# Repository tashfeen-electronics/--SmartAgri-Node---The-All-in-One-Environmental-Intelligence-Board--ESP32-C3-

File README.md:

# 🌾 SmartAgri Node — The All-in-One Environmental Intelligence Board— ESP32-C3 Environmental Monitoring PCB

A custom 4-layer PCB designed in KiCad for smart agriculture and environmental data logging — built around the **ESP32-C3-WROOM-02-H4**, with onboard sensing, local storage, and off-grid power management.

---

## 🚀 Overview

## 🌾 SmartAgri Node — The All-in-One Environmental Intelligence Board

*A masterclass in compact IoT engineering — built for the field, engineered for the future.*

Powered by the **ESP32-C3-WROOM-02-H4**, this board isn't just a sensor node — it's a complete edge-computing ecosystem packed into a single, elegant design. Whether you're building smart farms, weather networks, or next-gen IoT products, this board is your foundation.

### 🚀 Flagship Applications

- **🌱 Precision Agriculture Systems** — Real-time climate intelligence (temp, humidity, pressure, light) empowers farmers to optimize irrigation, planting, and harvest cycles like never before
- **☀️ Off-Grid Solar Monitoring Stations** — Autonomous, self-charging design (USB-C + battery + MCP73871 power management) means true "install and forget" reliability in remote locations
- **📡 Enterprise-Grade IoT Weather Networks** — Wi-Fi/BLE connectivity turns every unit into a live data point in a scalable, cloud-connected sensor mesh
- **💾 Mission-Critical Data Logging** — Onboard microSD ensures zero data loss, even in connectivity dead zones — perfect for research-grade field studies
- **🔊 Smart Environmental Surveillance** — Integrated mic input opens doors to acoustic monitoring: pest detection, livestock sounds, equipment health diagnostics
- **🔆 Intelligent Light Management** — TEMT6000 sensor enables automated greenhouse shading, grow-light control, and crop exposure analytics
- **🔌 Plug-and-Play Expansion Platform** — I2C/GPIO breakout headers make this a launchpad for custom sensor arrays: soil moisture, pH, EC, CO2, and beyond
- **🛡️ Industrial-Grade Power Protection** — ESD protection, fuse safeguarding, and regulated 3.3V rail deliver rock-solid reliability in harsh outdoor conditions
- **☁️ OTA-Ready Firmware Architecture** — Onboard SPI flash means remote fleets can be updated instantly — no truck rolls, no manual reflashing
- **🎓 Premier Prototyping & Education Platform** — USB-C programming, dedicated BOOT/RESET buttons, and SPI test points make this the go-to dev board for makers, students, and R&D teams alike

### 💎 Why This Board Stands Out

One design. Ten industries. Infinite possibilities — from **precision farming** to **smart cities**, **environmental research** to **industrial IoT**. This isn't just a PCB — it's a **scalable platform** ready to power the next generation of connected, autonomous sensing solutions.

---

## 🌾 Applications

- **Smart agriculture field monitoring** — logs temperature, humidity, pressure, and light intensity across crop fields or greenhouses
- **Solar/battery-powered remote sensor node** — runs unattended in the field, rechargeable via USB-C or solar panel
- **Soil/climate data logging station** — SD card backup for areas with weak or no Wi-Fi coverage
- **IoT weather station** — pushes live BME280 readings to a cloud dashboard or local server
- **Sunlight exposure tracking** — monitors sun exposure for crop growth optimization
- **Acoustic/pest monitoring** — mic input can detect insect activity, animal presence, or equipment sound
- **Expandable sensor hub** — I2C/GPIO headers for adding soil moisture, pH, or EC sensors
- **Battery-backed edge logger** — continues sensing during power outages or disconnection
- **OTA-capable firmware node** — onboard SPI flash supports remote firmware updates
- **General-purpose outdoor IoT dev board** — reusable prototyping platform beyond agriculture

---

## 🧩 Hardware Overview

### 🧠 Core Processing & Connectivity
| Component | Part | Purpose |
|---|---|---|
| U3 | ESP32-C3-WROOM-02-H4 | Main MCU — Wi-Fi/BLE, RISC-V core, chosen for wireless field data transmission without an external radio module |
| U4 | CP2102N | USB-to-UART bridge for programming/serial debug over USB-C |
| U2 | W25Q32JVSSIQ (32Mbit SPI Flash) | Extra non-volatile storage for OTA updates and log buffering |
| J3 | GSD090012SEU (microSD slot) | Local offline data logging when Wi-Fi is unavailable |

### 🌡️ Sensors
| Component | Part | Purpose |
|---|---|---|
| U6 | BME280 | Temperature, humidity & barometric pressure sensing |
| Q1 | TEMT6000X01 | Ambient light intensity sensing for crop exposure analysis |
| U7 | MAX4466EXK | Mic amplifier for acoustic sensing (pest/environmental sound) |

### 🔋 Power Management
| Component | Part | Purpose |
|---|---|---|
| J1 | USB-C (2338792-1) | Primary power/data input |
| J2 | JST connector (B2B-PH-SM4-TB) | Li-ion/LiPo battery input |
| U1 | MCP73871 | Battery charge management + power path — charges while running on USB |
| VR1 | LM1117MPX-3.3 | Regulates supply to a clean 3.3V rail |
| U5 | USBLC6-2SC6 | ESD protection on USB data lines |
| F1 | 0ZCH0110AF2E | Resettable fuse — overcurrent protection |
| Q2, Q3 | BC817 | Power switching/load gating for sleep-mode power savings |
| MK1 | CMC-5042PF-AC | Inductor/choke for power line filtering |

### 🕹️ User Interface
| Component | Part | Purpose |
|---|---|---|
| S1 | BOOT button | Puts ESP32 into flashing/bootloader mode |
| S2 | RESET button | Manual MCU reset |
| D1, D5 | Blue LEDs | Status indicators |
| D2, D6 | Green LEDs | Status indicators |
| D3, D4 | Red LEDs | Fault/error indicators |

### 🔧 Debug & Expansion
| Component | Purpose |
|---|---|
| TP1–TP5 | SPI bus test points (MOSI, MISO, SCLK, CS, CS-SD) for debugging flash/SD card |
| J4 | 4-pin header — I2C expansion (GND/SCL/SDA/3.3V) for external sensors |
| J5 | 5-pin header — additional GPIO/power expansion |

### ⚙️ Passives
- **Capacitors (C1–C25):** Decoupling and bulk capacitance for clean power delivery, especially during Wi-Fi transmit bursts
- **Resistors (R1–R35):** Pull-ups (I2C/reset lines), LED current limiting, and voltage divider/feedback networks

---

## 🧱 PCB Stackup — Why 4 Layers?

This board uses a **4-layer stackup (Signal / GND / PWR / Signal)** instead of a simpler 2-layer design, chosen specifically for better signal integrity given the mix of RF, digital, analog, and power circuitry on one small board.

**Benefits realized:**
- ✅ Dedicated, uninterrupted ground plane — critical for ESP32-C3 RF performance and reducing noise coupling into analog sensors
- ✅ Shorter, controlled return paths for high-speed SPI signals (flash + SD card), reducing EMI and reflections
- ✅ Dedicated power plane for cleaner, lower-impedance power delivery — especially during Wi-Fi TX current spikes
- ✅ Better isolation between noisy switching regulator circuitry and sensitive analog front-end (mic amp, light sensor)
- ✅ Tighter, more professional routing without sacrificing signal quality

---

## 🛠️ Tools Used

- **KiCad** — schematic capture, PCB layout, and 3D visualization

---

## 📸 Board Preview

*(Add board render/photo here)*

---

## 📋 Bill of Materials

Full BOM with quantities and footprints is available in <a href="https://github.com/tashfeen-electronics/--SmartAgri-Node---The-All-in-One-Environmental-Intelligence-Board--ESP32-C3-/blob/main/ESP32%20Project/bom/ibom.html" class="button">BOM</a>

---

## 📄 License

<a href="https://github.com/tashfeen-electronics/--SmartAgri-Node---The-All-in-One-Environmental-Intelligence-Board--ESP32-C3-/blob/main/LICENSE" class="button">
  ***LICENSE***
</a>

---

## 🙌 Author

**Tashfeen Electronics**
Designed with ❤️ in KiCad

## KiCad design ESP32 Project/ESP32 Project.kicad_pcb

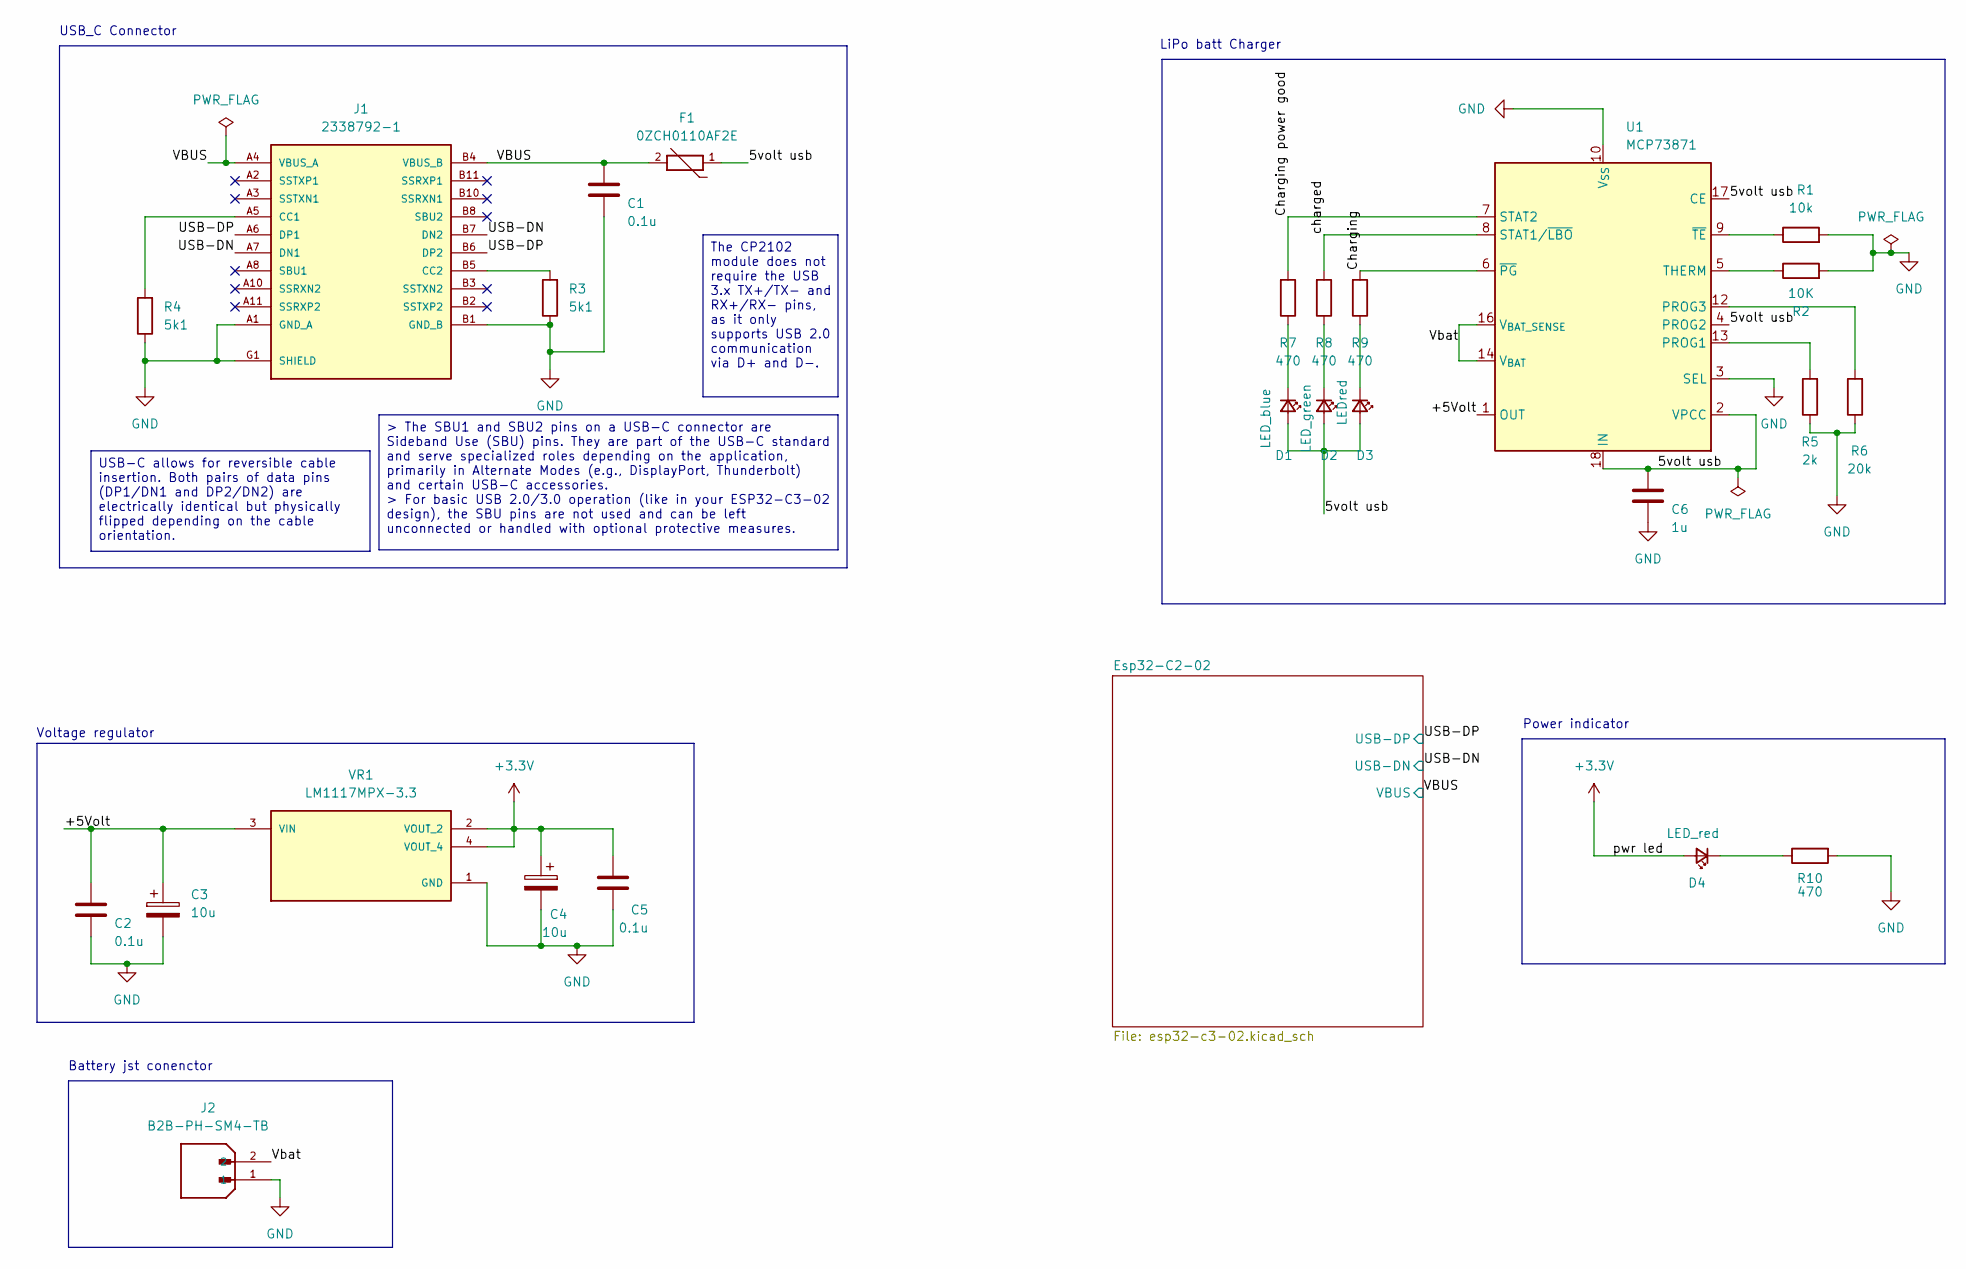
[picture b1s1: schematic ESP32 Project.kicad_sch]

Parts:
C1, C2, C5: 0.1u; C_0805_2012Metric
C3, C4: 10u; CP_EIA-3216-12_Kemet-S
C6: 1u; C_0805_2012Metric
D1: LED_blue; LED_0805_2012Metric_Pad1.15x1.40mm_HandSolder
D2: LED_green; LED_0805_2012Metric_Pad1.15x1.40mm_HandSolder
D3: LEDred; LED_0805_2012Metric_Pad1.15x1.40mm_HandSolder
D4: LED_red; LED_0805_2012Metric_Pad1.15x1.40mm_HandSolder
F1: 0ZCH0110AF2E; FUSC3225X100N; PARTREV Apr2023
J1: 2338792-1; TE_2338792-1; PARTREV A1
J2: B2B-PH-SM4-TB; JST_B2B-PH-SM4-TB; PARTREV N/A
R1: 10k; R_0805_2012Metric
R2: 10K; R_0805_2012Metric
R3, R4: 5k1; R_0805_2012Metric
R5: 2k; R_0805_2012Metric
R6: 20k; R_0805_2012Metric
R7, R8, R9, R10: 470; R_0805_2012Metric
U1: MCP73871; QFN-20-1EP_4x4mm_P0.5mm_EP2.5x2.5mm
VR1: LM1117MPX-3.3; VREG_LM1117MPX-3.3; PARTREV O

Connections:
+3.3V: C4.1, C5.1, D4.2 (A), VR1.2 (VOUT_2), VR1.4 (VOUT_4); also elsewhere on the board
/5volt usb: C6.1, D1.2 (A), D2.2 (A), D3.2 (A), F1.1, U1.2 (VPCC), U1.4 (PROG2), U1.17 (CE), U1.18 (IN), U1.19 (IN)
/+5Volt: C2.1, C3.1, U1.1 (OUT), U1.20 (OUT), VR1.3 (VIN)
/Charging: R9.2, U1.6 (~PG)
/Charging power good: R7.2, U1.7 (STAT2)
/USB-DN: J1.A7 (DN1), J1.B7 (DN2); also elsewhere on the board
/USB-DP: J1.A6 (DP1), J1.B6 (DP2); also elsewhere on the board
/Vbat: J2.2, U1.14 (V_{BAT}), U1.15 (V_{BAT}), U1.16 (V_{BAT_SENSE})
/charged: R8.2, U1.8 (STAT1/~LBO)
GND: C1.2, C2.2, C3.2, C4.2, C5.2, C6.2, J1.A1 (GND_A), J1.A12 (GND_A), J1.B1 (GND_B), J1.B12 (GND_B), J1.G1 (SHIELD), J1.G2 (SHIELD), J1.G3 (SHIELD), J1.G4 (SHIELD), J1.G5 (SHIELD), J1.G6 (SHIELD), J2.1, R1.2, R2.2, R3.1, R4.1, R5.1, R6.1, R10.2, U1.3 (SEL), U1.10 (V_{SS}), U1.11 (V_{SS}), U1.21 (V_{SS}), VR1.1 (GND); also elsewhere on the board
unnamed: D1.1 (K), R7.1
unnamed: D2.1 (K), R8.1
unnamed: D3.1 (K), R9.1
unnamed: D4.1 (K), R10.1
unnamed: J1.A5 (CC1), R4.2
unnamed: J1.B5 (CC2), R3.2
unnamed: R5.2, U1.13 (PROG1)
unnamed: R6.2, U1.12 (PROG3)
unnamed: R2.1, U1.5 (THERM)
unnamed: R1.1, U1.9 (~TE)
VBUS_A: C1.1, F1.2, J1.A4 (VBUS_A), J1.A9 (VBUS_A), J1.B4 (VBUS_B), J1.B9 (VBUS_B); also elsewhere on the board

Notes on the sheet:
Power indicator
USB_C Connector
Voltage regulator
LiPo batt Charger
Battery jst conenctor
USB-C allows for reversible cable insertion. Both pairs of data pins (DP1/DN1 and DP2/DN2) are electrically identical but physically flipped depending on the cable orientation.
The CP2102 module does not require the USB 3.x TX+/TX- and RX+/RX- pins, as it only supports USB 2.0 communication via D+ and D-.
> The SBU1 and SBU2 pins on a USB-C connector are Sideband Use (SBU) pins. They are part of the USB-C standard and serve specialized roles depending on the application, primarily in Alternate Modes (e.g., DisplayPort, Thunderbolt) and certain USB-C accessories. > For basic USB 2.0/3.0 operation (li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

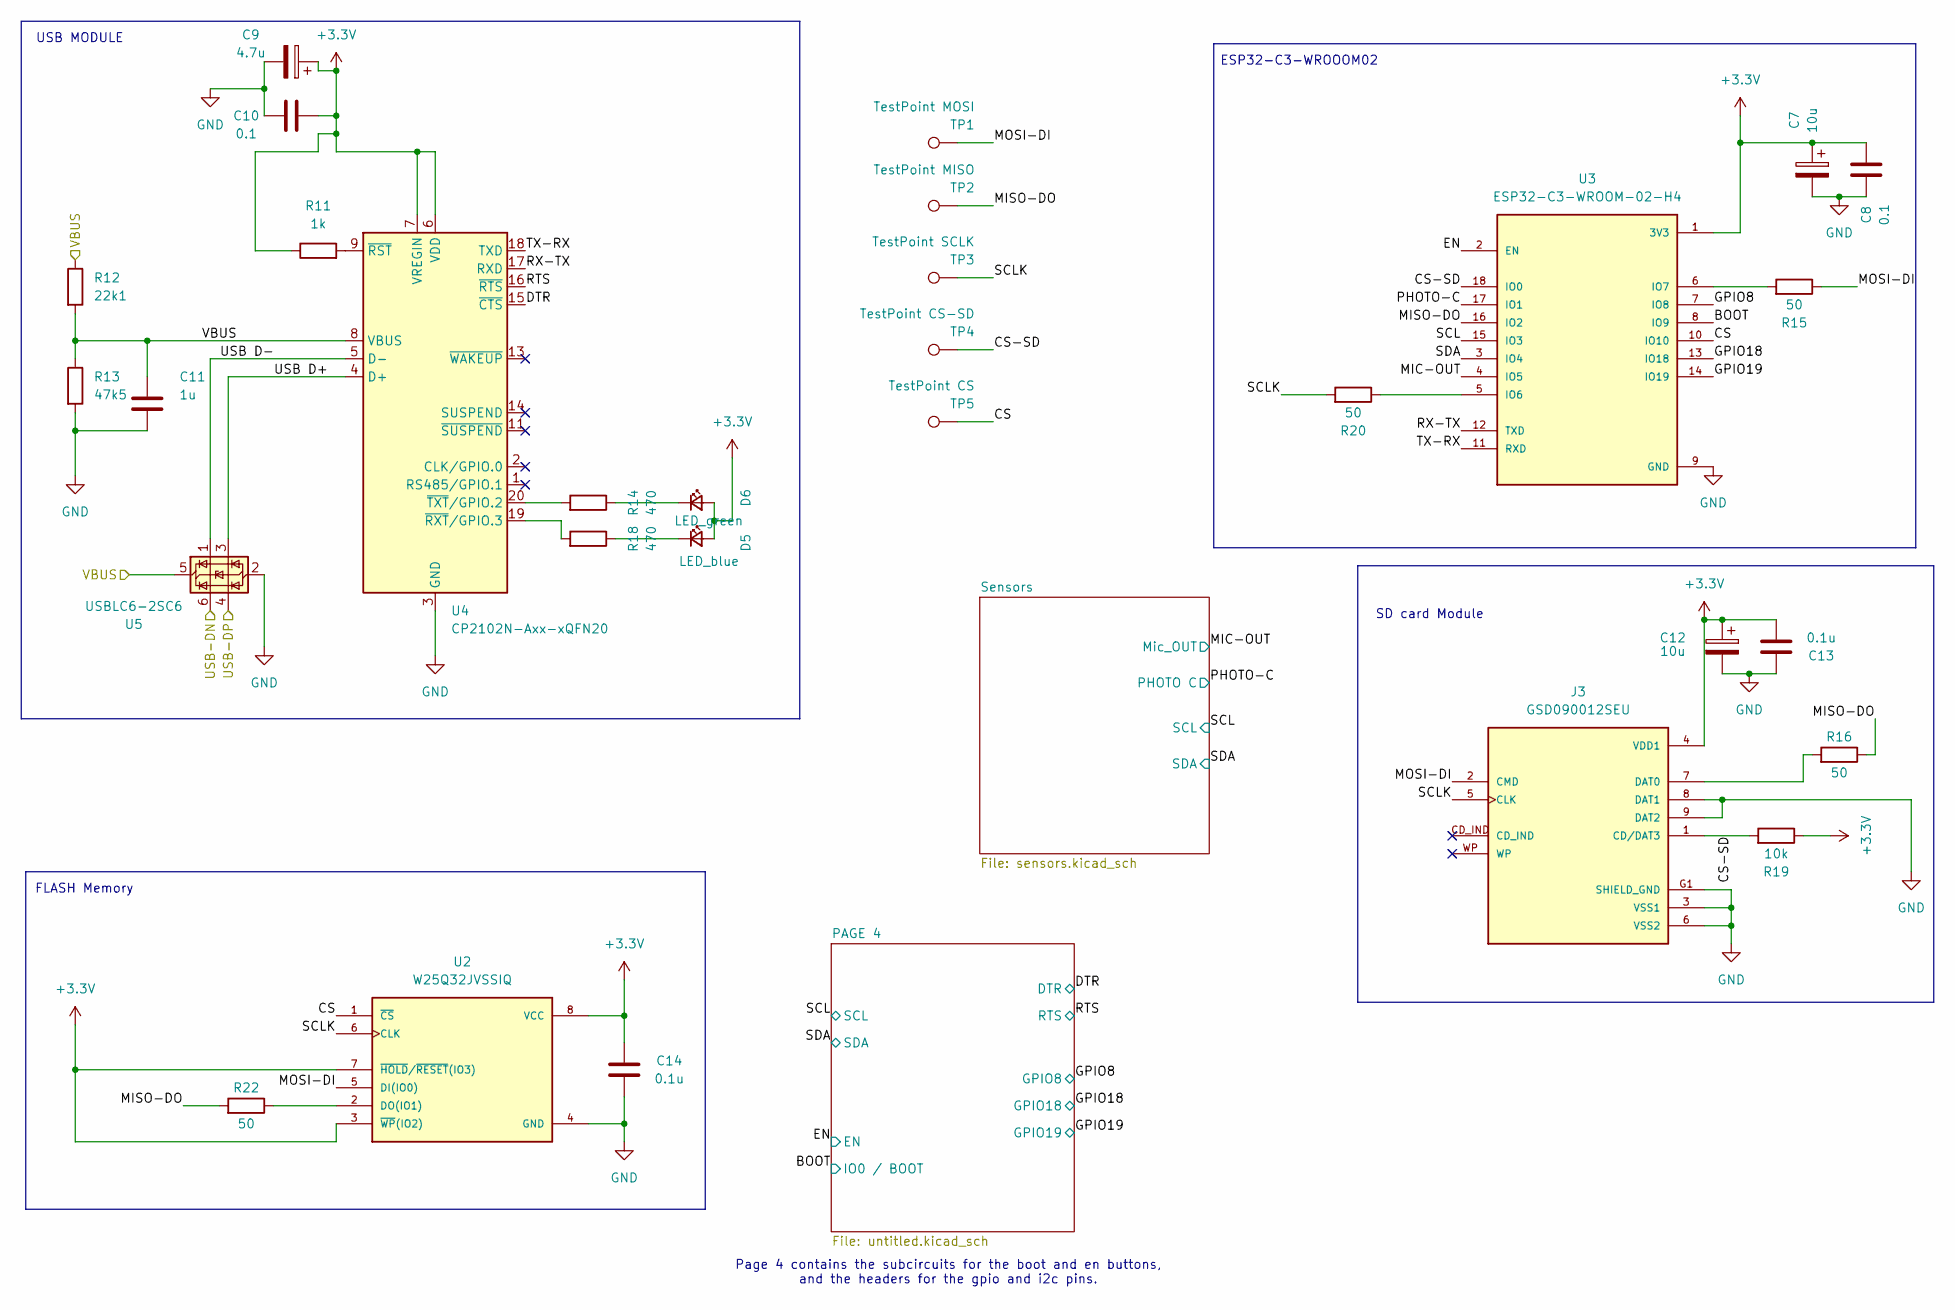
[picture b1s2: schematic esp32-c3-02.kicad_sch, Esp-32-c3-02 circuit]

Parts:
C7, C12: 10u; CP_EIA-3216-12_Kemet-S
C8, C10: 0.1; C_0805_2012Metric
C9: 4.7u; CP_EIA-3216-12_Kemet-S
C11: 1u; C_0805_2012Metric
C13, C14: 0.1u; C_0805_2012Metric
D5: LED_blue; LED_0805_2012Metric_Pad1.15x1.40mm_HandSolder
D6: LED_green; LED_0805_2012Metric_Pad1.15x1.40mm_HandSolder
J3: GSD090012SEU; AMPHENOL_GSD090012SEU; PARTREV E
R11: 1k; R_0805_2012Metric
R12: 22k1; R_0805_2012Metric
R13: 47k5; R_0805_2012Metric
R14, R18: 470; R_0805_2012Metric
R15, R16, R20, R22: 50; R_0805_2012Metric
R19: 10k; R_0805_2012Metric
TP1: TestPoint MOSI; TestPoint_Pad_D1.0mm
TP2: TestPoint MISO; TestPoint_Pad_D1.0mm
TP3: TestPoint SCLK; TestPoint_Pad_D1.0mm
TP4: TestPoint CS-SD; TestPoint_Pad_D1.0mm
TP5: TestPoint CS; TestPoint_Pad_D1.0mm
U2: W25Q32JVSSIQ; SOIC127P790X216-8N; M_PART_NUMBER W25QXX
U3: ESP32-C3-WROOM-02-H4; MODULE_ESP32-C3-WROOM-02-H4
U4: CP2102N-Axx-xQFN20; QFN-20-1EP_3x3mm_P0.45mm_EP1.6x1.6mm
U5: USBLC6-2SC6; SOT-23-6

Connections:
+3.3V: C7.1, C8.1, C9.1, C10.1, C12.1, C13.1, C14.2, D5.2 (A), D6.2 (A), J3.4 (VDD1), R11.1, R19.1, U2.3 (~WP(IO2)), U2.7 (~HOLD/~RESET(IO3)), U2.8 (VCC), U3.1 (3V3), U4.6 (VDD), U4.7 (VREGIN); also elsewhere on the board
/Esp32-C2-02/BOOT: U3.8 (IO9); also elsewhere on the board
/Esp32-C2-02/CS: TP5.1 (1_1), U2.1 (~CS), U3.10 (IO10)
/Esp32-C2-02/CS-SD: J3.1 (CD/DAT3), R19.2, TP4.1 (1_1), U3.18 (IO0)
/Esp32-C2-02/DTR: U4.15 (~CTS); also elsewhere on the board
/Esp32-C2-02/EN: U3.2 (EN); also elsewhere on the board
/Esp32-C2-02/GPIO8: U3.7 (IO8); also elsewhere on the board
/Esp32-C2-02/GPIO18: U3.13 (IO18); also elsewhere on the board
/Esp32-C2-02/GPIO19: U3.14 (IO19); also elsewhere on the board
/Esp32-C2-02/MIC-OUT: U3.4 (IO5); also elsewhere on the board
/Esp32-C2-02/MISO-DO: R16.1, R22.2, TP2.1 (1_1), U3.16 (IO2)
/Esp32-C2-02/MOSI-DI: J3.2 (CMD), R15.1, TP1.1 (1_1), U2.5 (DI(IO0))
/Esp32-C2-02/PHOTO-C: U3.17 (IO1); also elsewhere on the board
/Esp32-C2-02/RTS: U4.16 (~RTS); also elsewhere on the board
/Esp32-C2-02/RX-TX: U3.12 (TXD), U4.17 (RXD)
/Esp32-C2-02/SCL: U3.15 (IO3); also elsewhere on the board
/Esp32-C2-02/SCLK: J3.5 (CLK), R20.2, TP3.1 (1_1), U2.6 (CLK)
/Esp32-C2-02/SDA: U3.3 (IO4); also elsewhere on the board
/Esp32-C2-02/TX-RX: U3.11 (RXD), U4.18 (TXD)
/Esp32-C2-02/USB D+: U4.4 (D+), U5.3 (I/O2)
/Esp32-C2-02/USB D-: U4.5 (D-), U5.1 (I/O1)
/USB-DN: U5.6 (I/O1); also elsewhere on the board
/USB-DP: U5.4 (I/O2); also elsewhere on the board
GND: C7.2, C8.2, C9.2, C10.2, C11.2, C12.2, C13.2, C14.1, J3.3 (VSS1), J3.6 (VSS2), J3.8 (DAT1), J3.9 (DAT2), J3.G1 (SHIELD_GND), J3.G2 (SHIELD_GND), J3.G3 (SHIELD_GND), J3.G4 (SHIELD_GND), R13.2, U2.4 (GND), U3.9 (GND), U3.19 (GND), U3.20 (GND), U3.21 (GND), U3.22 (GND), U3.23 (GND), U3.24 (GND), U3.25 (GND), U3.26 (GND), U3.27 (GND), U3.28 (GND), U3.29 (GND), U3.30 (GND), U3.31 (GND), U3.32 (GND), U3.33 (GND), U3.34 (GND), U3.35 (GND), U3.36 (GND), U3.37 (GND), U3.38 (GND), U3.39 (GND), U4.3 (GND), U4.12 (GND), U4.21 (GND), U5.2 (GND); also elsewhere on the board
unnamed: D5.1 (K), R18.1
unnamed: D6.1 (K), R14.1
unnamed: J3.7 (DAT0), R16.2
unnamed: R22.1, U2.2 (DO(IO1))
unnamed: R20.1, U3.5 (IO6)
unnamed: R15.2, U3.6 (IO7)
unnamed: R11.2, U4.9 (~RST)
unnamed: R18.2, U4.19 (~RXT/GPIO.3)
unnamed: R14.2, U4.20 (~TXT/GPIO.2)
VBUS_A: C11.1, R12.1, R12.2, R13.1, U4.8 (VBUS), U5.5 (VBUS); also elsewhere on the board

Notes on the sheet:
USB MODULE
SD card Module
Page 4 contains the subcircuits for the boot and en buttons, and the headers for the gpio and i2c pins.
ESP32-C3-WROOOM02
FLASH Memory

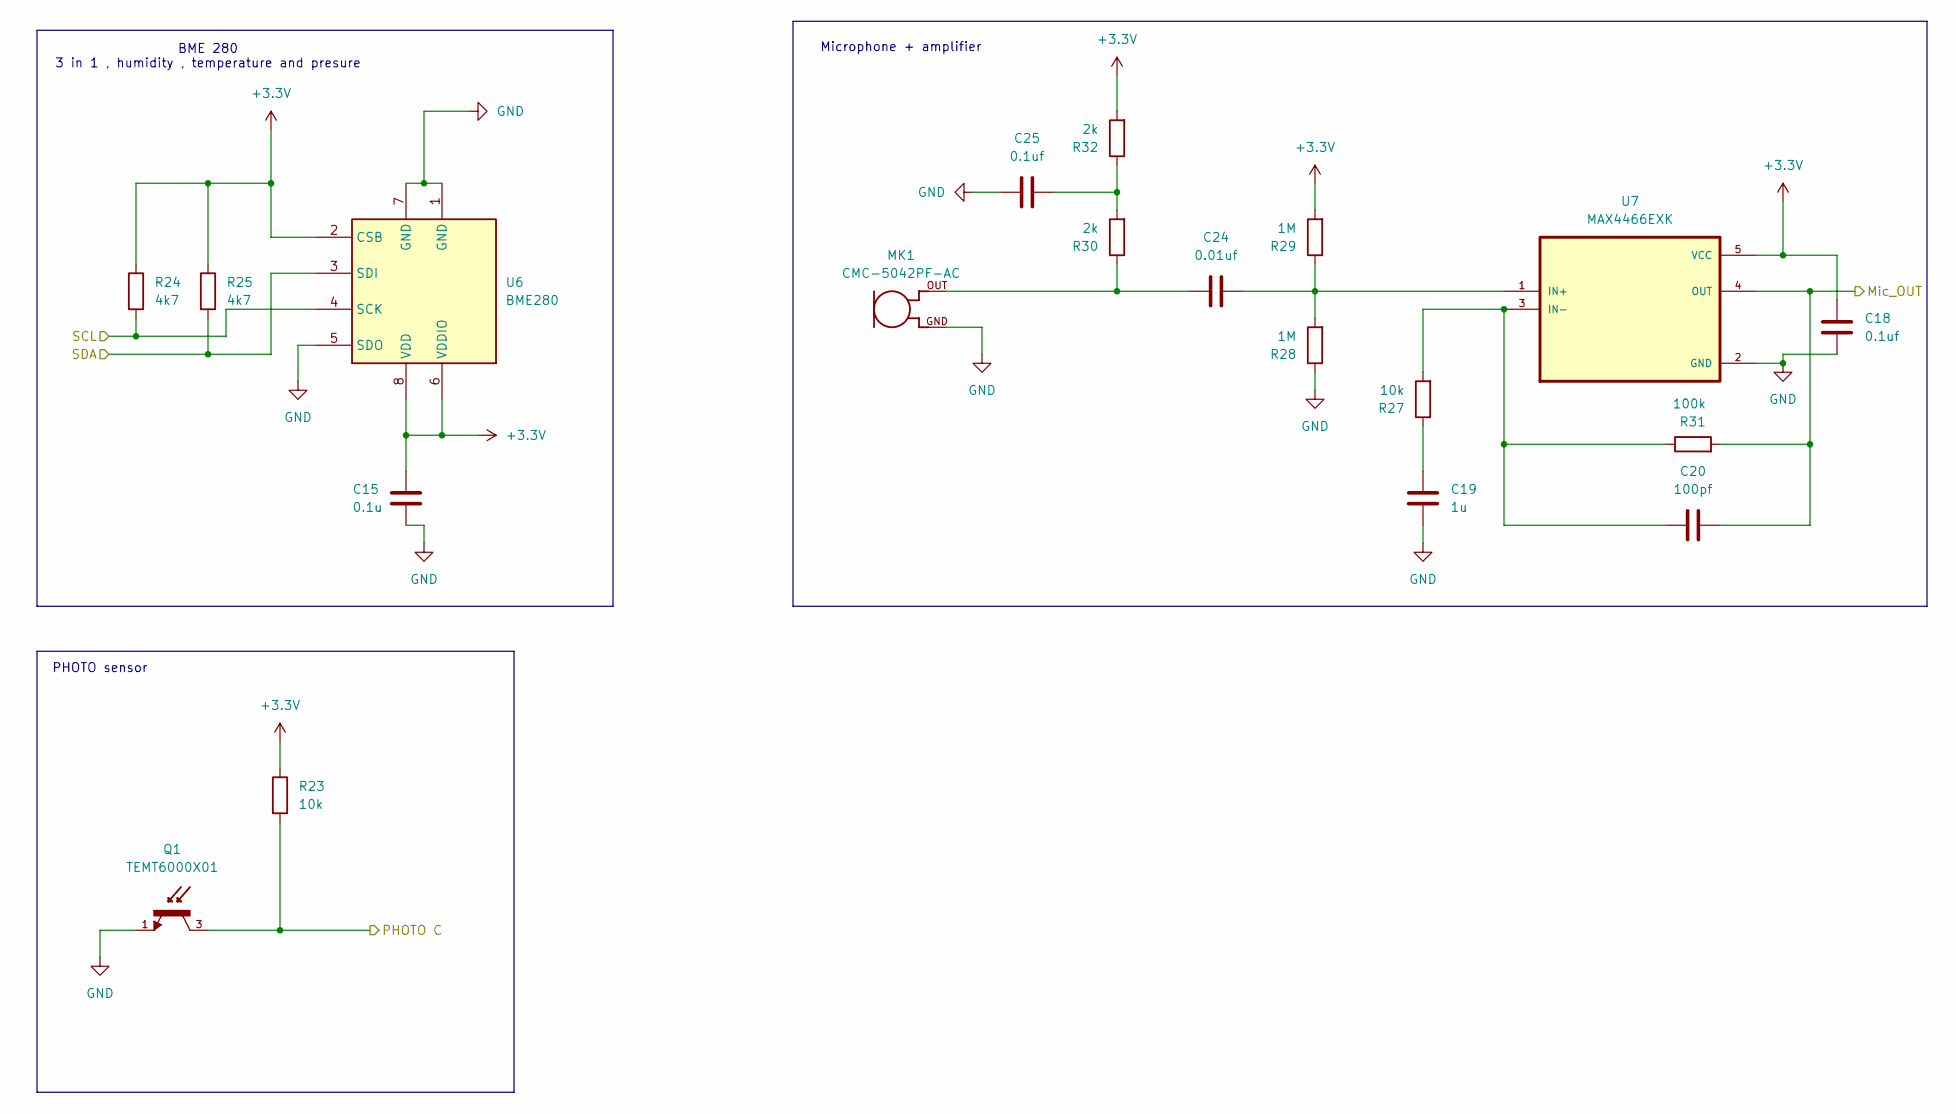
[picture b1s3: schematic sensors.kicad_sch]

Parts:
C15: 0.1u; C_0805_2012Metric
C18, C25: 0.1uf; C_0805_2012Metric
C19: 1u; C_0805_2012Metric
C20: 100pf; C_0805_2012Metric
C24: 0.01uf; C_0805_2012Metric
MK1: CMC-5042PF-AC; CUI_CMC-5042PF-AC
Q1: TEMT6000X01; TRANS_TEMT6000X01; PARTREV 1.9
R23, R27: 10k; R_0805_2012Metric
R24, R25: 4k7; R_0805_2012Metric
R28, R29: 1M; R_0805_2012Metric
R30, R32: 2k; R_0805_2012Metric
R31: 100k; R_0805_2012Metric
U6: BME280; Bosch_LGA-8_2.5x2.5mm_P0.65mm_ClockwisePinNumbering
U7: MAX4466EXK; SOT65P210X110-5N; DigiKey_Part_Number MAX4466EXK+CT-ND

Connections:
+3.3V: C15.2, C18.2, R23.1, R24.1, R25.1, R29.2, R32.2, U6.2 (CSB), U6.6 (VDDIO), U6.8 (VDD), U7.5 (VCC); also elsewhere on the board
/Esp32-C2-02/MIC-OUT: C20.1, R31.2, U7.4 (OUT); also elsewhere on the board
/Esp32-C2-02/PHOTO-C: Q1.3, R23.2; also elsewhere on the board
/Esp32-C2-02/SCL: R24.2, U6.4 (SCK); also elsewhere on the board
/Esp32-C2-02/SDA: R25.2, U6.3 (SDI); also elsewhere on the board
GND: C15.1, C18.1, C19.2, C25.2, MK1.GND, Q1.1, R28.1, U6.1 (GND), U6.5 (SDO), U6.7 (GND), U7.2 (GND); also elsewhere on the board
unnamed: C19.1, R27.1
unnamed: C24.2, MK1.OUT, R30.1
unnamed: C25.1, R30.2, R32.1
unnamed: C24.1, R28.2, R29.1, U7.1 (IN+)
unnamed: C20.2, R27.2, R31.1, U7.3 (IN-)

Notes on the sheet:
BME 280 3 in 1 , humidity , temperature and presure
PHOTO sensor
Microphone + amplifier

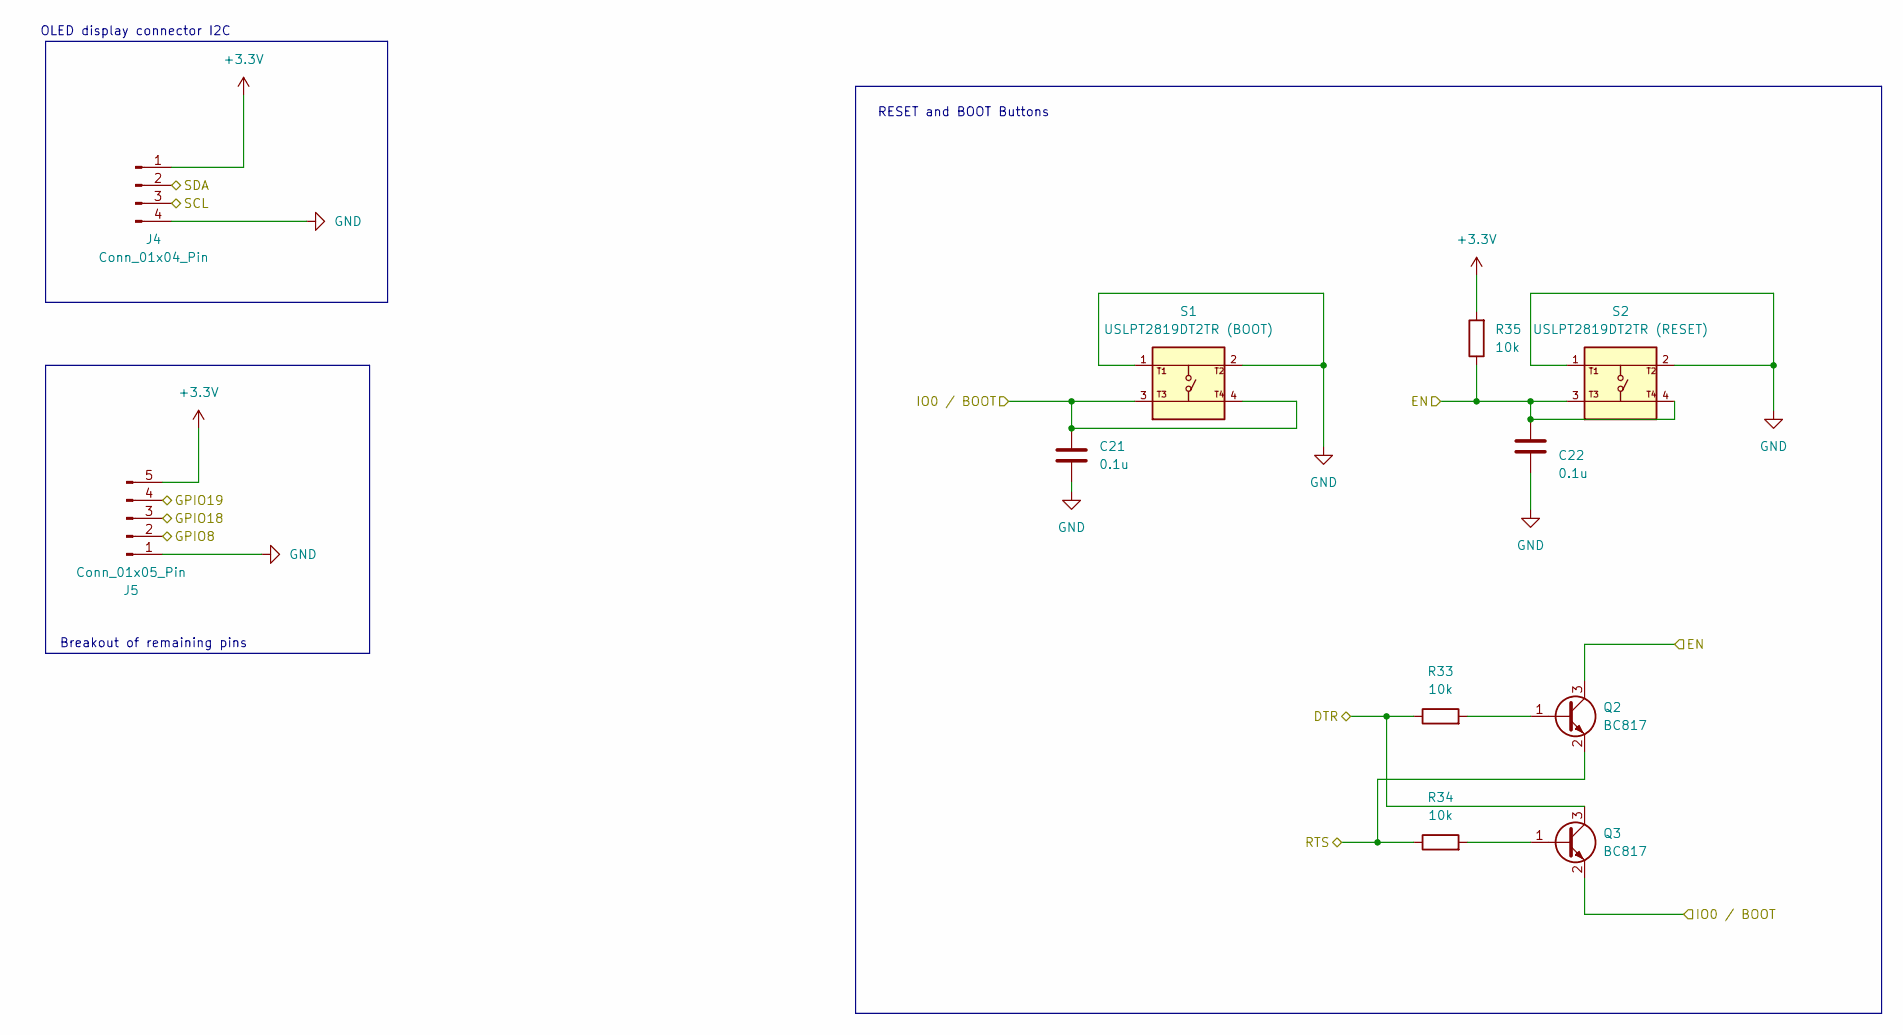
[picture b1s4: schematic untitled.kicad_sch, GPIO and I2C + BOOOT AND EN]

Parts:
C21, C22: 0.1u; C_0805_2012Metric
J4: Conn_01x04_Pin; PinHeader_1x04_P2.54mm_Vertical
J5: Conn_01x05_Pin; PinHeader_1x05_P2.54mm_Vertical
Q2, Q3: BC817; SOT-23
R33, R34, R35: 10k; R_0805_2012Metric
S1: USLPT2819DT2TR (BOOT); SW_USLPT2819DT2TR; PARTREV P
S2: USLPT2819DT2TR (RESET); SW_USLPT2819DT2TR; PARTREV P

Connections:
+3.3V: J4.1, J5.5, R35.2; also elsewhere on the board
/Esp32-C2-02/BOOT: C21.1, Q3.2 (E), S1.3, S1.4; also elsewhere on the board
/Esp32-C2-02/DTR: Q3.3 (C), R33.1; also elsewhere on the board
/Esp32-C2-02/EN: C22.1, Q2.3 (C), R35.1, S2.3, S2.4; also elsewhere on the board
/Esp32-C2-02/GPIO8: J5.2; also elsewhere on the board
/Esp32-C2-02/GPIO18: J5.3; also elsewhere on the board
/Esp32-C2-02/GPIO19: J5.4; also elsewhere on the board
/Esp32-C2-02/RTS: Q2.2 (E), R34.1; also elsewhere on the board
/Esp32-C2-02/SCL: J4.3; also elsewhere on the board
/Esp32-C2-02/SDA: J4.2; also elsewhere on the board
GND: C21.2, C22.2, J4.4, J5.1, S1.1, S1.2, S2.1, S2.2; also elsewhere on the board
unnamed: Q2.1 (B), R33.2
unnamed: Q3.1 (B), R34.2

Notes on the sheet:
RESET and BOOT Buttons
OLED display connector I2C
Breakout of remaining pins

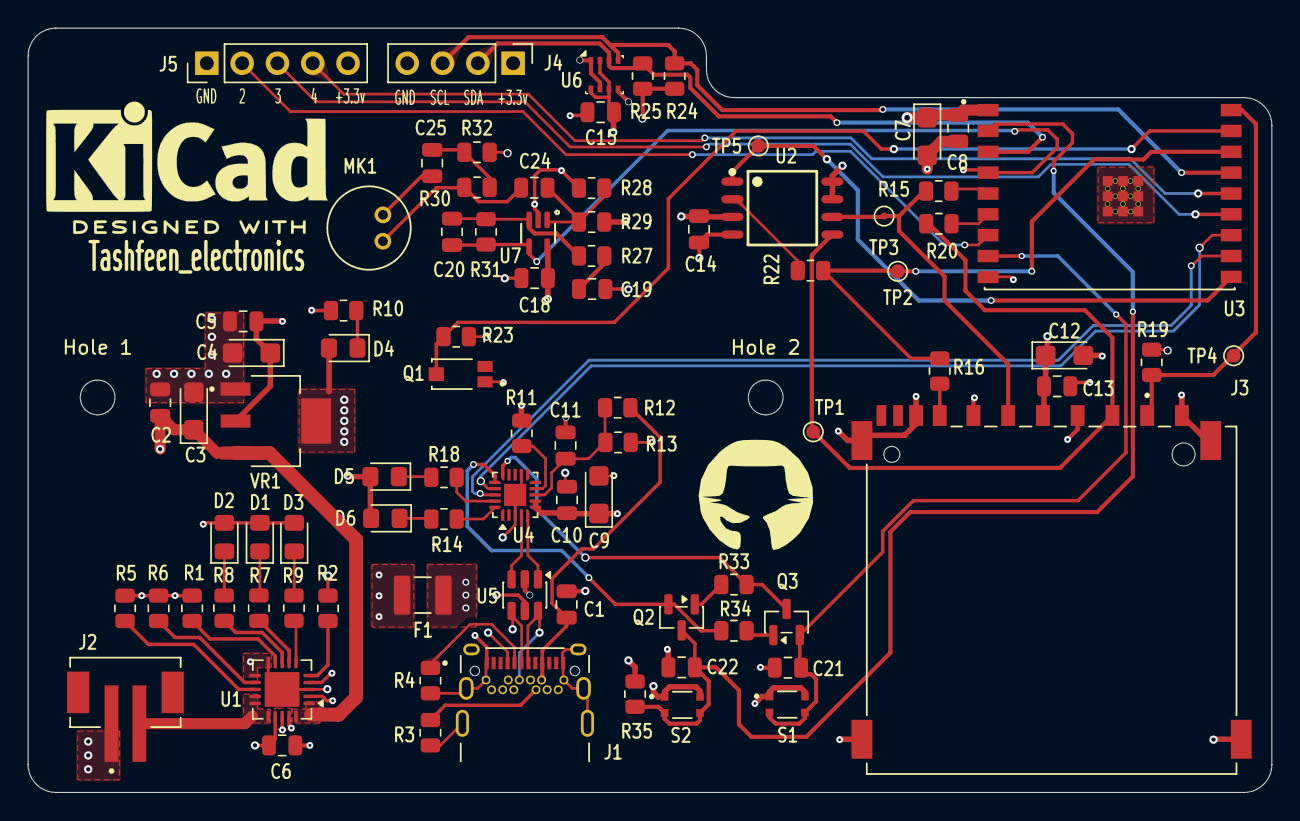
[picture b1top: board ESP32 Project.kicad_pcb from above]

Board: 4 copper layers, 89.5 x 55.0 mm, 87 parts (0 on the bottom side), 57 nets.

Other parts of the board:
Hole 1, Hole 2: MountingHole_2.5mm
